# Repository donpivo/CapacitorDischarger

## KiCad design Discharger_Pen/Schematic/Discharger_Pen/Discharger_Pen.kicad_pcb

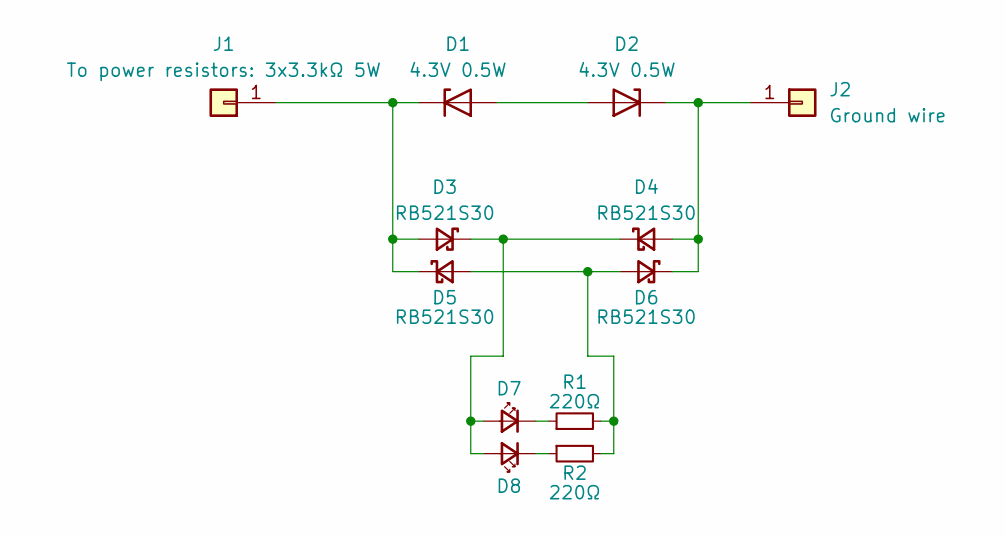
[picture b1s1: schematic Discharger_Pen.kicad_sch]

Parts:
D1, D2: 4.3V 0.5W; D_SOD-123
D3, D4, D5, D6: RB521S30; D_SOD-523
D7, D8: 0805 Blue; LED_0805_2012Metric_Pad1.15x1.40mm_HandSolder
J1: To power resistors: 3x3.3kΩ 5W; TestPoint_THTPad_3.0x3.0mm_Drill1.5mm
J2: Ground wire; TestPoint_THTPad_3.0x3.0mm_Drill1.5mm
R1, R2: 220Ω; R_0805_2012Metric_Pad1.20x1.40mm_HandSolder

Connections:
unnamed: D1.2 (A), D2.2 (A)
unnamed: D1.1 (K), D3.2 (A), D5.1 (K), J1.1
unnamed: D2.1 (K), D4.2 (A), D6.1 (K), J2.1
unnamed: D3.1 (K), D4.1 (K), D7.2 (A), D8.2 (A)
unnamed: D5.2 (A), D6.2 (A), R1.2, R2.2
unnamed: D7.1 (K), R1.1
unnamed: D8.1 (K), R2.1

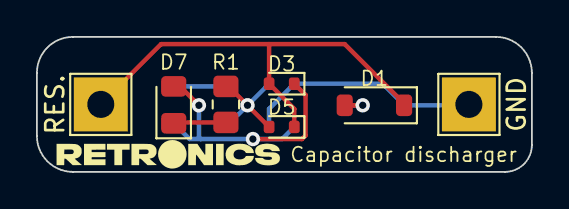
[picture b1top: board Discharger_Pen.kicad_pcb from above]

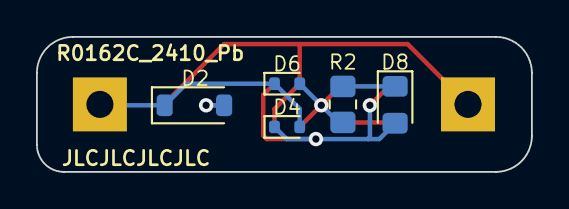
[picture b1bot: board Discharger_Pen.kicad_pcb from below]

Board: 2 copper layers, 27.5 x 7.5 mm, 12 parts (5 on the bottom side), 7 nets.

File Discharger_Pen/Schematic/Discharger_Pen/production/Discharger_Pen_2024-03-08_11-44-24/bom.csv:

Designator,Footprint,Quantity,Value,LCSC Part #
D1,D_SOD-123,1, 4.3V 0.5W,
D2,D_SOD-123,1,4.3V 0.5W,
"D3, D4, D5, D6",D_SOD-523,4,RB521S30,
"D7, D8",0805,2,0805 Blue,
J1,TestPoint_THTPad_3.0x3.0mm_Drill1.5mm,1,To power resistors: 3x3.3kΩ 5W,
J2,TestPoint_THTPad_3.0x3.0mm_Drill1.5mm,1,Ground wire,
"R1, R2",0805,2,220Ω,

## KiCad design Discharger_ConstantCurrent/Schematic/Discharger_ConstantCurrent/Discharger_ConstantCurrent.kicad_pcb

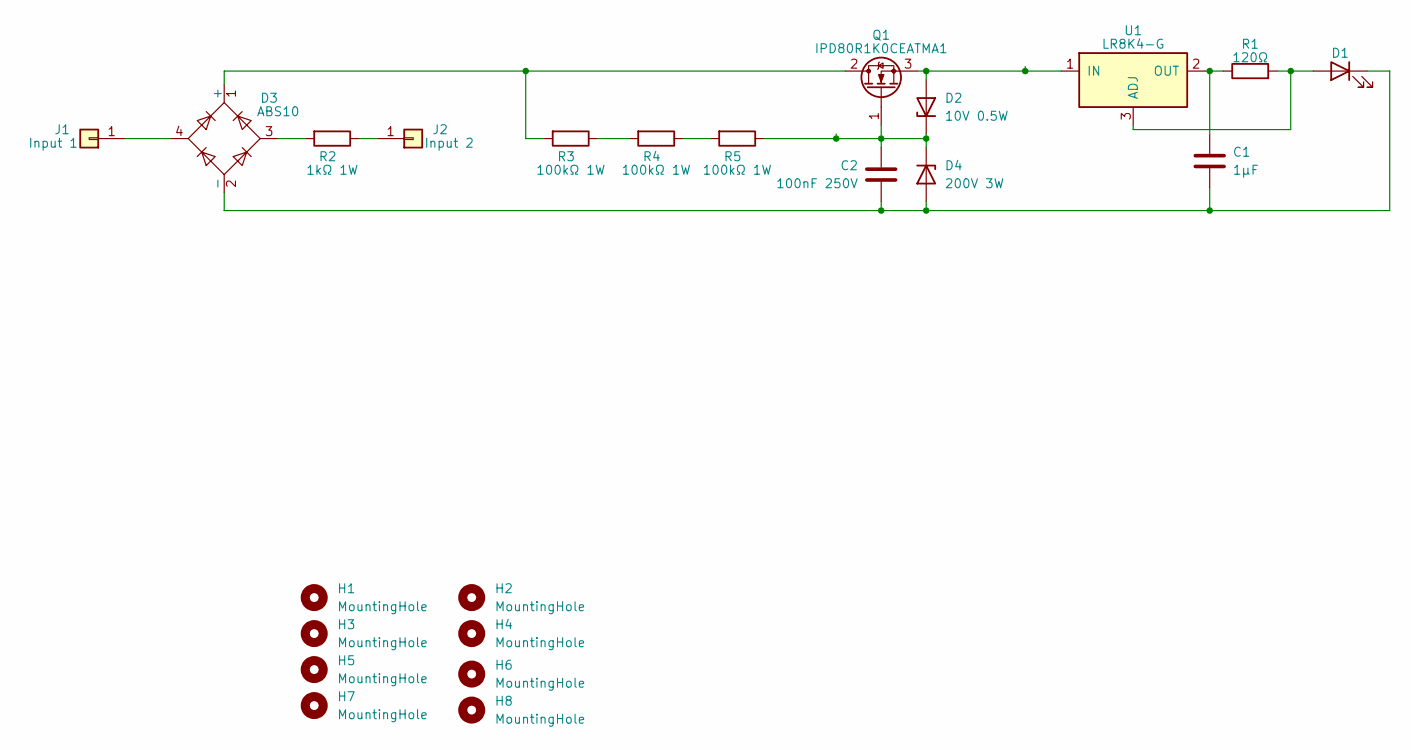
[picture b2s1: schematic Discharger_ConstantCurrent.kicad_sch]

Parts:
C1: 1µF; C_0805_2012Metric_Pad1.18x1.45mm_HandSolder
C2: 100nF 250V; C_1206_3216Metric_Pad1.33x1.80mm_HandSolder
D1: LED_1206_3216Metric_Pad1.42x1.75mm_HandSolder
D2: 10V 0.5W; D_SOD-123
D3: ABS10; Diode_Bridge_Diotec_ABS
D4: 200V 3W; D_SMB_Handsoldering
H1, H2, H3, H4, H5, H6, H7, H8: MountingHole; MountingHole_3.2mm_M3
J1: Input 1; TestPoint_Pad_D4.0mm
J2: Input 2; TestPoint_Pad_D4.0mm
Q1: IPD80R1K0CEATMA1; TO-252-2
R1: 120Ω; R_0805_2012Metric_Pad1.20x1.40mm_HandSolder
R2: 1kΩ 1W; R_2512_6332Metric_Pad1.40x3.35mm_HandSolder
R3, R4, R5: 100kΩ 1W; R_2512_6332Metric_Pad1.40x3.35mm_HandSolder
U1: LR8K4-G; TO-252-2

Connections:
unnamed: D1.2 (A), R1.2, U1.3 (ADJ)
unnamed: C1.2, C2.2, D1.1 (K), D3.2 (-), D4.2 (A)
unnamed: D2.2 (A), Q1.3 (S), U1.1 (IN)
unnamed: C2.1, D2.1 (K), D4.1 (K), Q1.1 (G), R5.1
unnamed: D3.1 (+), Q1.2 (D), R3.2
unnamed: D3.3, R2.2
unnamed: D3.4, J1.1
unnamed: J2.1, R2.1
unnamed: R3.1, R4.2
unnamed: R4.1, R5.2
unnamed: C1.1, R1.1, U1.2 (OUT)

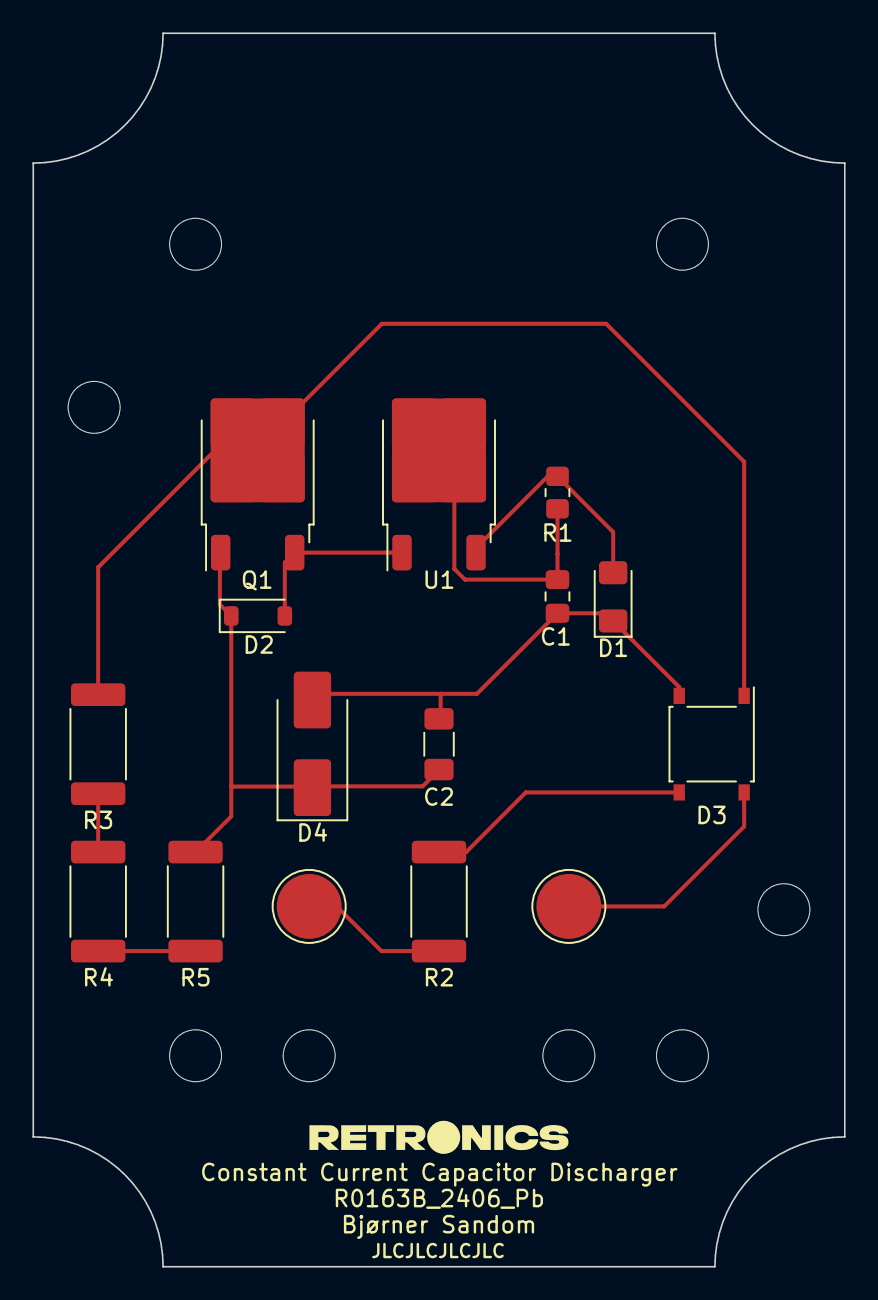
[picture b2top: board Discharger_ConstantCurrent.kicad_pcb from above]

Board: 2 copper layers, 50.0 x 76.0 mm, 23 parts (0 on the bottom side), 11 nets.

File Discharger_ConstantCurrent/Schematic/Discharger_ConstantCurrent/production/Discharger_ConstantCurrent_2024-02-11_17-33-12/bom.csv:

Designator,Footprint,Quantity,Value,LCSC Part #
C1,0805,1,1µF,
C2,1206,1,100nF 250V,
D1,1206,1,~,
D2,D_SOD-123,1,10V 0.5W,
D3,Diode_Bridge_Diotec_ABS,1,ABS10,
D4,D_SMB_Handsoldering,1,200V 3W,
"H1, H2, H3, H4, H5, H6, H7, H8",MountingHole_3.2mm_M3,8,MountingHole,
J1,TestPoint_Pad_D4.0mm,1,Input 1,
J2,TestPoint_Pad_D4.0mm,1,Input 2,
Q1,TO-252-2,1,IPD80R1K0CEATMA1,
R1,0805,1,120Ω,
R2,2512,1,1kΩ 1W,
"R3, R4, R5",2512,3,100kΩ 1W,
U1,TO-252-2,1,LR8K4-G,

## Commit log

2024-03-29 File cleanup
